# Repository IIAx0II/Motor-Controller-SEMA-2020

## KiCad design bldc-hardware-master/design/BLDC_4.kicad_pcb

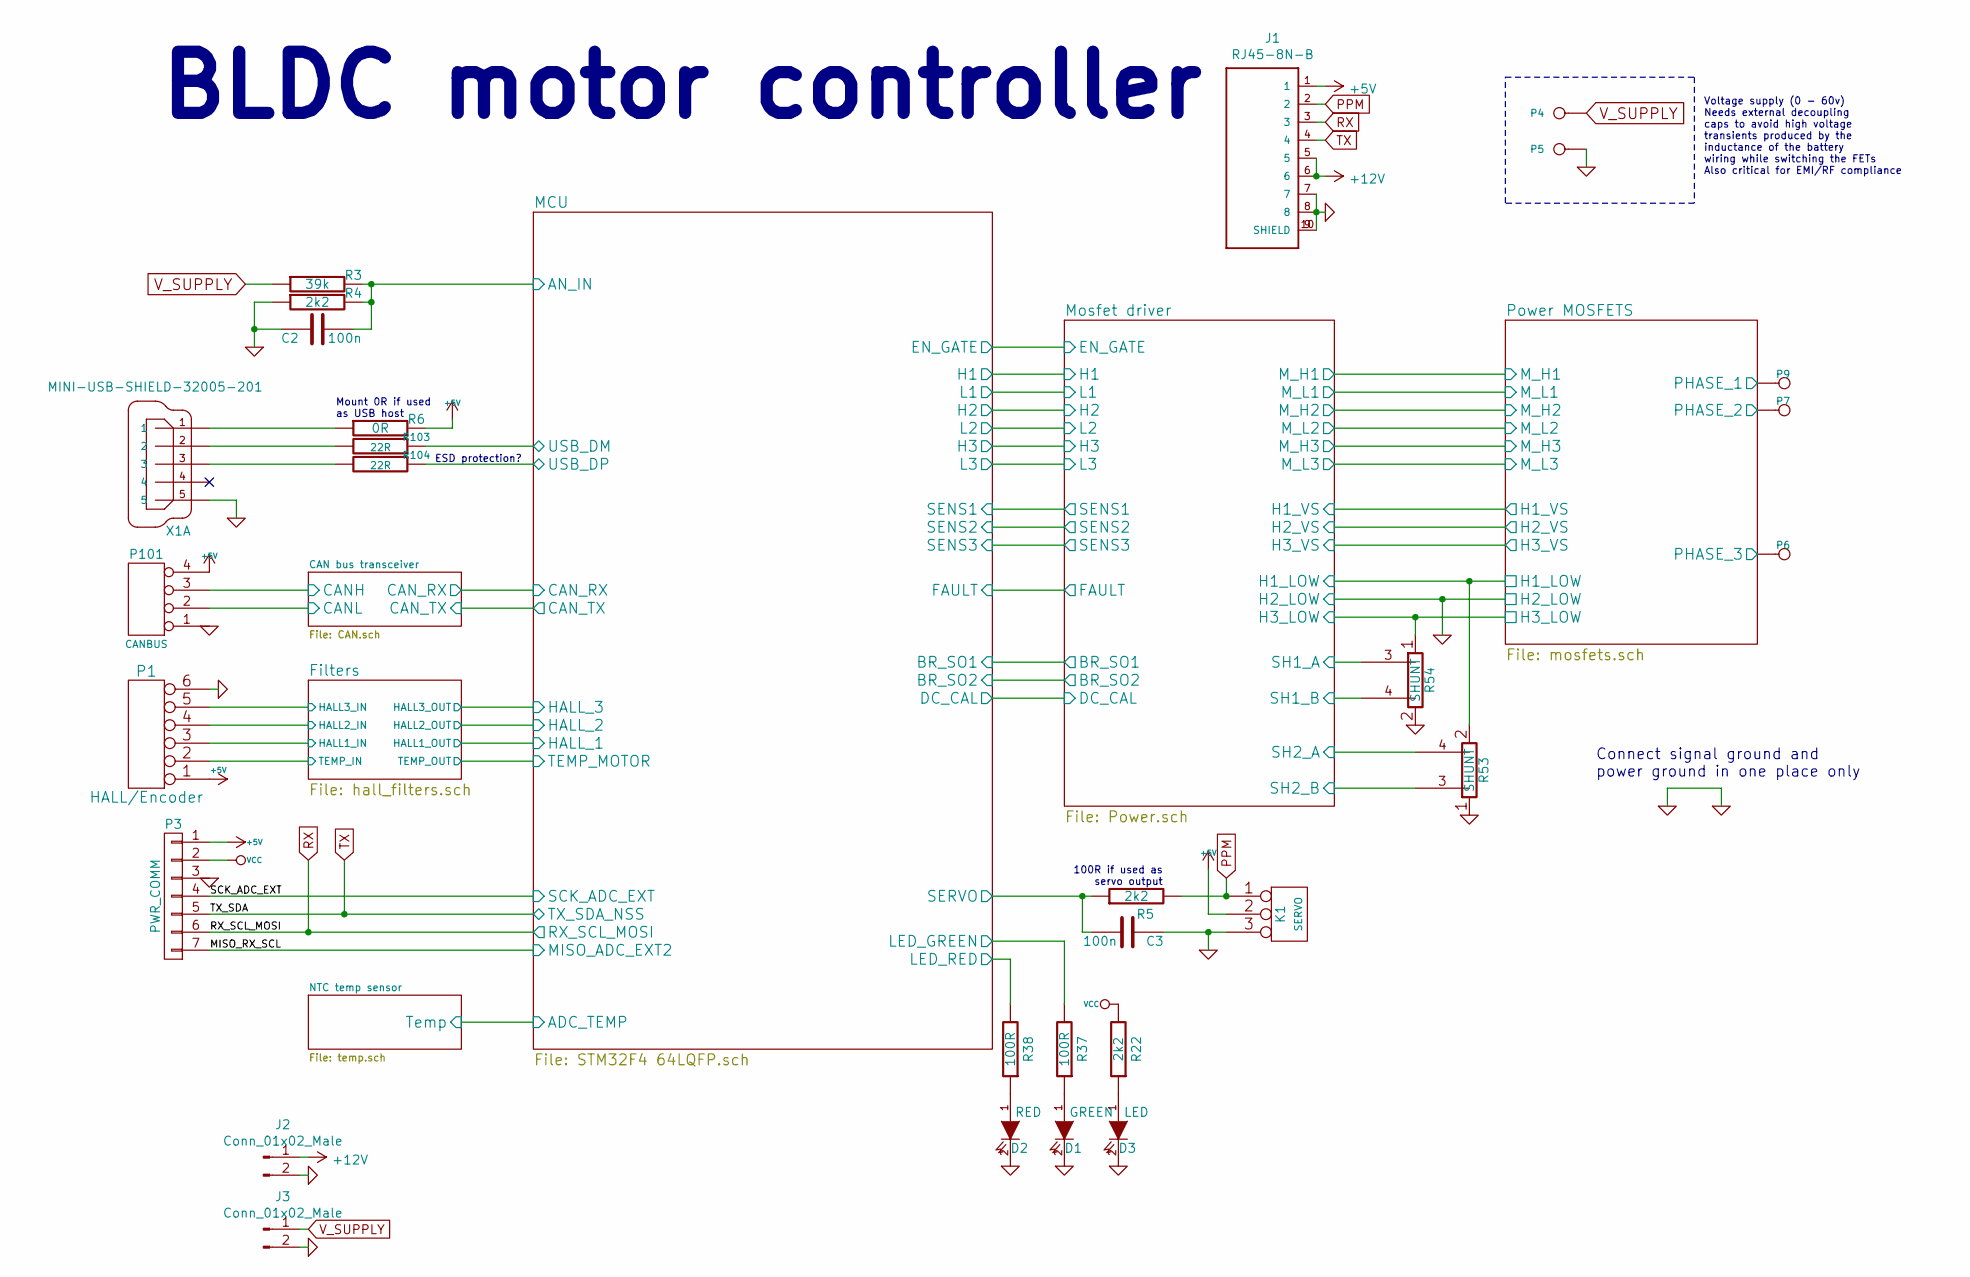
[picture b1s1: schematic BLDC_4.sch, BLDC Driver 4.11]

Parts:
C2, C3: 100n; SMD-0603_c
D1: GREEN; LED-0603
D2: RED; LED-0603
D3: LED; LED-0603
J1: RJ45-8N-B; TE_RJ45-8N-B
J2, J3: Conn_01x02_Male; Molex_Mini-Fit_Jr_5566-02A2_2x01_P4.20mm_Vertical
K1: SERVO; pinhead-1X03
P1: HALL/Encoder; MICRO_JST_6
P3: PWR_COMM; b7b-ph-kl
P4: IN+; 1PAD_4x5mm
P5: IN-; 1PAD_4x5mm
P6: MOTOR1; 1PAD_4x5mm
P7: MOTOR2; 1PAD_4x5mm
P9: MOTOR3; 1PAD_4x5mm
P101: CANBUS; b4b-ph-kl
R3: 39k; SMD-0603_r
R4, R5, R22: 2k2; SMD-0603_r
R6: 0R; SMD-0603_r
R37, R38: 100R; SMD-0603_r
R53, R54: SHUNT; WSLP2726
R103, R104: 22R; SMD-0603_r
X1: MINI-USB-SHIELD-32005-201; USB-UX60R-MB-5ST

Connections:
+5V: J1.1, K1.2 (PM), P1.1, P3.1, P101.4, R6.2; also elsewhere on the board
+12V: J1.5, J1.6, J2.1
/CAN bus transceiver/CANH: P101.3; also elsewhere on the board
/CAN bus transceiver/CANL: P101.2; also elsewhere on the board
/Filters/HALL1_IN: P1.3; also elsewhere on the board
/Filters/HALL2_IN: P1.4; also elsewhere on the board
/Filters/HALL3_IN: P1.5; also elsewhere on the board
/Filters/TEMP_IN: P1.2; also elsewhere on the board
/MCU/AN_IN: C2.2, R3.2, R4.2; also elsewhere on the board
/MCU/LED_GREEN: R37.2; also elsewhere on the board
/MCU/LED_RED: R38.2; also elsewhere on the board
/MCU/SERVO: C3.2, R5.1; also elsewhere on the board
/MCU/USB_DM: R103.1; also elsewhere on the board
/MCU/USB_DP: R104.1; also elsewhere on the board
/MISO_RX_SCL: P3.7; also elsewhere on the board
/Mosfet driver/H1_LOW: R53.2; also elsewhere on the board
/Mosfet driver/H1_VS: P9.1; also elsewhere on the board
/Mosfet driver/H2_VS: P7.1; also elsewhere on the board
/Mosfet driver/H3_LOW: R54.1; also elsewhere on the board
/Mosfet driver/H3_VS: P6.1; also elsewhere on the board
/Mosfet driver/SH1_A: R54.3; also elsewhere on the board
/Mosfet driver/SH1_B: R54.4; also elsewhere on the board
/Mosfet driver/SH2_A: R53.4; also elsewhere on the board
/Mosfet driver/SH2_B: R53.3; also elsewhere on the board
/SCK_ADC_EXT: P3.4; also elsewhere on the board
unnamed: D1.1 (A), R37.1
unnamed: D2.1 (A), R38.1
unnamed: D3.1 (A), R22.1
unnamed: R6.1, X1.1
unnamed: R103.2, X1.2
unnamed: R104.2, X1.3
PPM: J1.2, K1.1, R5.2
RX: J1.3, P3.6; also elsewhere on the board
TX: J1.4, P3.5; also elsewhere on the board
VCC: P3.2, R22.2; also elsewhere on the board
V_SUPPLY: J3.1, P4.1, R3.1; also elsewhere on the board

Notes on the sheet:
100R if used as servo output
Mount 0R if used as USB host
ESD protection?
BLDC motor controller
Voltage supply (0 - 60v) Needs external decoupling caps to avoid high voltage transients produced by the inductance of the battery wiring while switching the FETs Also critical for EMI/RF compliance
Connect signal ground and power ground in one place only

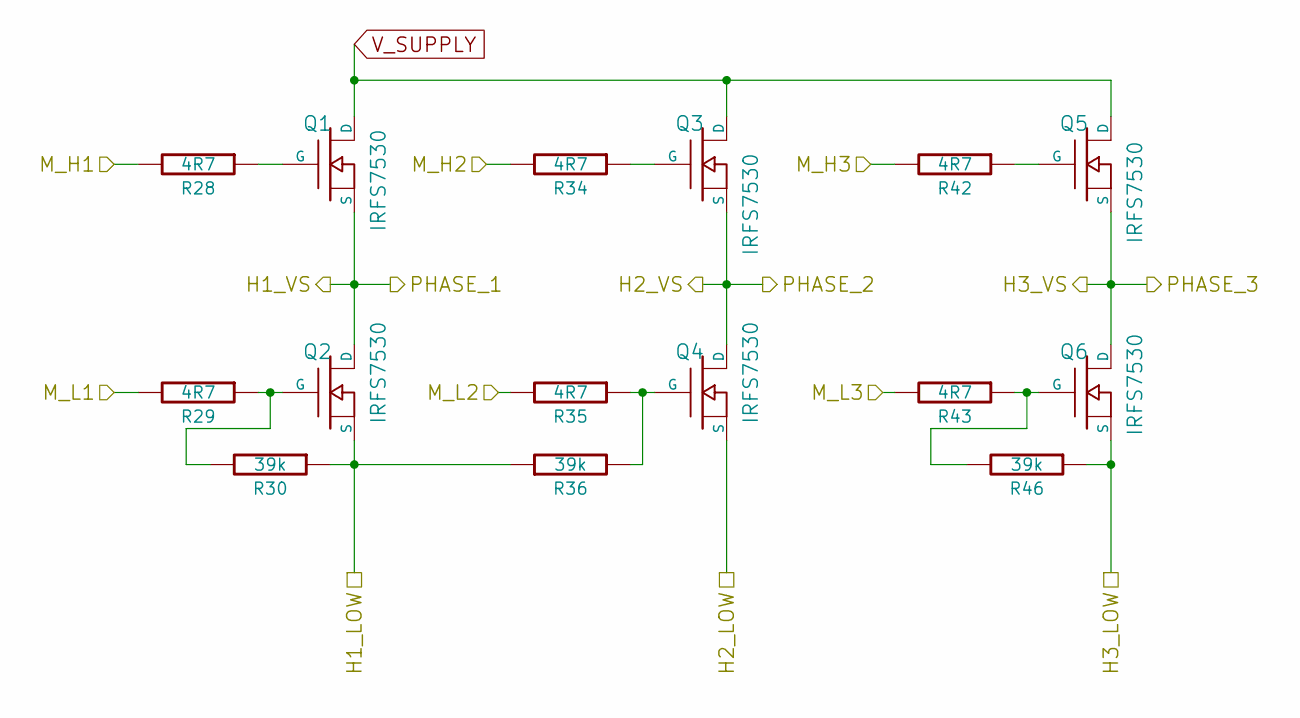
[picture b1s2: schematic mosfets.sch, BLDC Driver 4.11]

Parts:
Q1, Q2, Q3, Q4, Q5, Q6: IRFS7530; D2PAK-7-GDS
R28, R29, R34, R35, R42, R43: 4R7; SMD-0603_r
R30, R36, R46: 39k; SMD-0603_r

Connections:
/Mosfet driver/H1_LOW: Q2.S, R30.1, R36.1; also elsewhere on the board
/Mosfet driver/H1_VS: Q1.S, Q2.D; also elsewhere on the board
/Mosfet driver/H2_VS: Q3.S, Q4.D; also elsewhere on the board
/Mosfet driver/H3_LOW: Q6.S, R46.1; also elsewhere on the board
/Mosfet driver/H3_VS: Q5.S, Q6.D; also elsewhere on the board
/Mosfet driver/M_H1: R28.2; also elsewhere on the board
/Mosfet driver/M_H2: R34.2; also elsewhere on the board
/Mosfet driver/M_H3: R42.2; also elsewhere on the board
/Mosfet driver/M_L1: R29.2; also elsewhere on the board
/Mosfet driver/M_L2: R35.2; also elsewhere on the board
/Mosfet driver/M_L3: R43.2; also elsewhere on the board
unnamed: Q1.G, R28.1
unnamed: Q2.G, R29.1, R30.2
unnamed: Q3.G, R34.1
unnamed: Q4.G, R35.1, R36.2
unnamed: Q5.G, R42.1
unnamed: Q6.G, R43.1, R46.2
V_SUPPLY: Q1.D, Q3.D, Q5.D; also elsewhere on the board

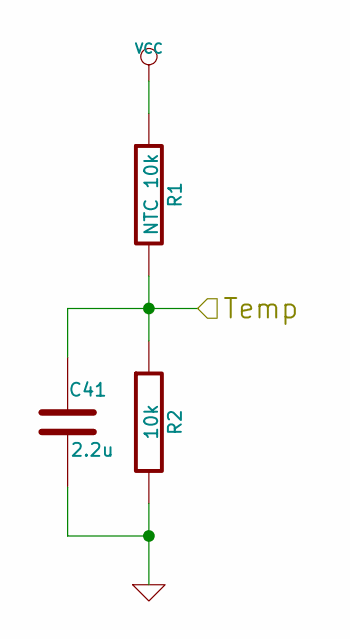
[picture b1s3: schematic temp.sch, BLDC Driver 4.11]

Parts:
C41: 2.2u; SMD-0603_c
R1: NTC 10k; SMD-0603_r
R2: 10k; SMD-0603_r

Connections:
/MCU/ADC_TEMP: C41.1, R1.2, R2.1; also elsewhere on the board
VCC: R1.1; also elsewhere on the board

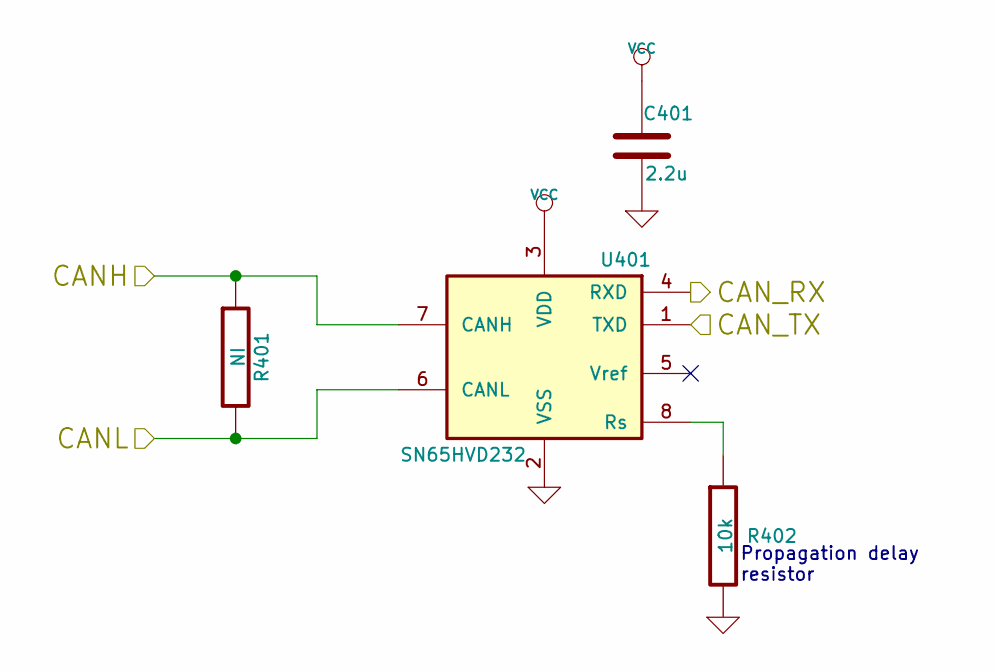
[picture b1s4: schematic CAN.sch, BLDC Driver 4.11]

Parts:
C401: 2.2u; SMD-0603_c
R401: NI; SMD-0603_r
R402: 10k; SMD-0603_r
U401: SN65HVD232; SOIC-8-W

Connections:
/CAN bus transceiver/CANH: R401.1, U401.7 (CANH); also elsewhere on the board
/CAN bus transceiver/CANL: R401.2, U401.6 (CANL); also elsewhere on the board
/CAN bus transceiver/CAN_RX: U401.4 (RXD); also elsewhere on the board
/CAN bus transceiver/CAN_TX: U401.1 (TXD); also elsewhere on the board
unnamed: R402.1, U401.8 (Rs)
VCC: C401.1, U401.3 (VDD); also elsewhere on the board

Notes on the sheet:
Propagation delay resistor

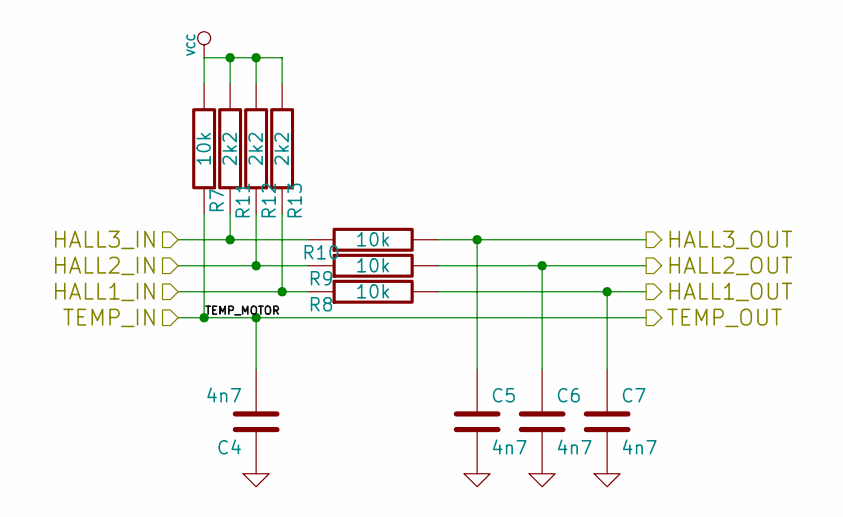
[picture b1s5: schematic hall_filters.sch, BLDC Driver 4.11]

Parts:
C4, C5, C6, C7: 4n7; SMD-0603_c
R7, R8, R9, R10: 10k; SMD-0603_r
R11, R12, R13: 2k2; SMD-0603_r

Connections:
/Filters/HALL1_IN: R8.1, R13.1; also elsewhere on the board
/Filters/HALL1_OUT: C7.1, R8.2; also elsewhere on the board
/Filters/HALL2_IN: R9.1, R12.1; also elsewhere on the board
/Filters/HALL2_OUT: C6.1, R9.2; also elsewhere on the board
/Filters/HALL3_IN: R10.1, R11.1; also elsewhere on the board
/Filters/HALL3_OUT: C5.1, R10.2; also elsewhere on the board
/Filters/TEMP_IN: C4.2, R7.1; also elsewhere on the board
VCC: R7.2, R11.2, R12.2, R13.2; also elsewhere on the board

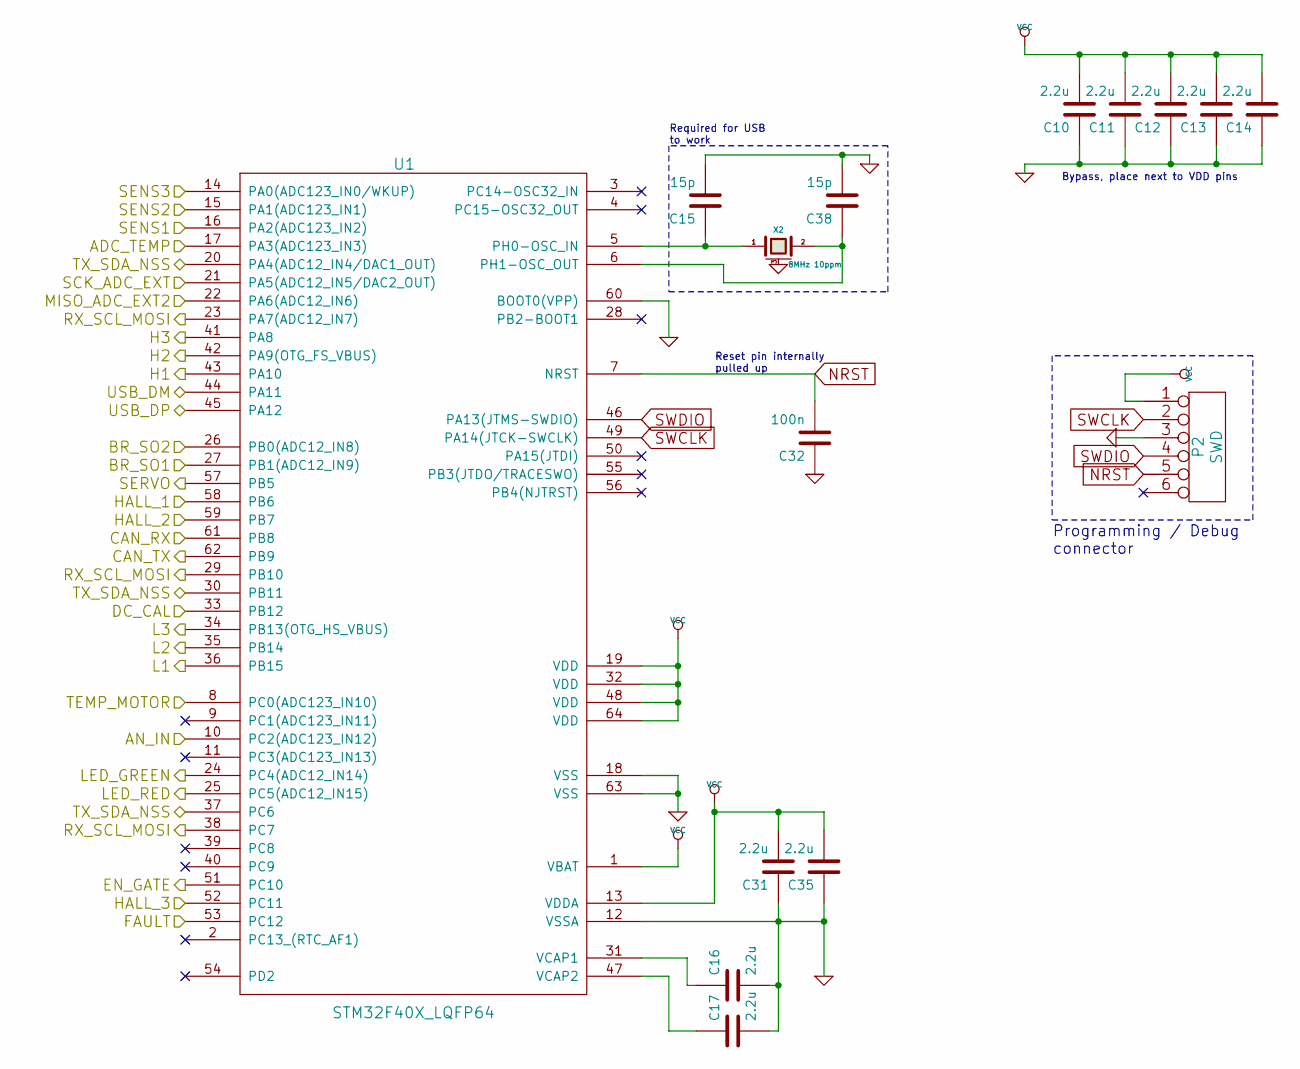
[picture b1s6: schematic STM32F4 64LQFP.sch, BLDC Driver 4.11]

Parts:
C10, C11, C12, C13, C14, C16, C17, C31, C35: 2.2u; SMD-0603_c
C15, C38: 15p; SMD-0603_c
C32: 100n; SMD-0603_c
P2: SWD; MICRO_JST_6
U1: STM32F40X_LQFP64; lqfp64_pad_mod
X2: 8MHz 10ppm; Crystal_5x3mm; mfg# ABM3B-8.0-10-1UT

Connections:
/CAN bus transceiver/CAN_RX: U1.61 (PB8); also elsewhere on the board
/CAN bus transceiver/CAN_TX: U1.62 (PB9); also elsewhere on the board
/Filters/HALL1_OUT: U1.58 (PB6); also elsewhere on the board
/Filters/HALL2_OUT: U1.59 (PB7); also elsewhere on the board
/Filters/HALL3_OUT: U1.52 (PC11); also elsewhere on the board
/Filters/TEMP_IN: U1.8 (PC0(ADC123_IN10)); also elsewhere on the board
/MCU/ADC_TEMP: U1.17 (PA3(ADC123_IN3)); also elsewhere on the board
/MCU/AN_IN: U1.10 (PC2(ADC123_IN12)); also elsewhere on the board
/MCU/BR_SO1: U1.27 (PB1(ADC12_IN9)); also elsewhere on the board
/MCU/BR_SO2: U1.26 (PB0(ADC12_IN8)); also elsewhere on the board
/MCU/DC_CAL: U1.33 (PB12); also elsewhere on the board
/MCU/EN_GATE: U1.51 (PC10); also elsewhere on the board
/MCU/FAULT: U1.53 (PC12); also elsewhere on the board
/MCU/H1: U1.43 (PA10); also elsewhere on the board
/MCU/H2: U1.42 (PA9(OTG_FS_VBUS)); also elsewhere on the board
/MCU/H3: U1.41 (PA8); also elsewhere on the board
/MCU/L1: U1.36 (PB15); also elsewhere on the board
/MCU/L2: U1.35 (PB14); also elsewhere on the board
/MCU/L3: U1.34 (PB13(OTG_HS_VBUS)); also elsewhere on the board
/MCU/LED_GREEN: U1.24 (PC4(ADC12_IN14)); also elsewhere on the board
/MCU/LED_RED: U1.25 (PC5(ADC12_IN15)); also elsewhere on the board
/MCU/SENS1: U1.16 (PA2(ADC123_IN2)); also elsewhere on the board
/MCU/SENS2: U1.15 (PA1(ADC123_IN1)); also elsewhere on the board
/MCU/SENS3: U1.14 (PA0(ADC123_IN0/WKUP)); also elsewhere on the board
/MCU/SERVO: U1.57 (PB5); also elsewhere on the board
/MCU/USB_DM: U1.44 (PA11); also elsewhere on the board
/MCU/USB_DP: U1.45 (PA12); also elsewhere on the board
/MISO_RX_SCL: U1.22 (PA6(ADC12_IN6)); also elsewhere on the board
/SCK_ADC_EXT: U1.21 (PA5(ADC12_IN5/DAC2_OUT)); also elsewhere on the board
NRST: C32.2, P2.5, U1.7 (NRST)
unnamed: C15.1, U1.5 (PH0-OSC_IN), X2.1
unnamed: C16.1, U1.31 (VCAP1)
unnamed: C17.1, U1.47 (VCAP2)
unnamed: C38.1, U1.6 (PH1-OSC_OUT), X2.2
RX: U1.23 (PA7(ADC12_IN7)), U1.29 (PB10), U1.38 (PC7); also elsewhere on the board
SWCLK: P2.2, U1.49 (PA14(JTCK-SWCLK))
SWDIO: P2.4, U1.46 (PA13(JTMS-SWDIO))
TX: U1.20 (PA4(ADC12_IN4/DAC1_OUT)), U1.30 (PB11), U1.37 (PC6); also elsewhere on the board
VCC: C10.2, C11.2, C12.2, C13.2, C14.2, C31.2, C35.2, P2.1, U1.1 (VBAT), U1.13 (VDDA), U1.19 (VDD), U1.32 (VDD), U1.48 (VDD), U1.64 (VDD); also elsewhere on the board

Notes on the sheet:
Programming / Debug connector
Reset pin internally pulled up
Required for USB to work
Bypass, place next to VDD pins

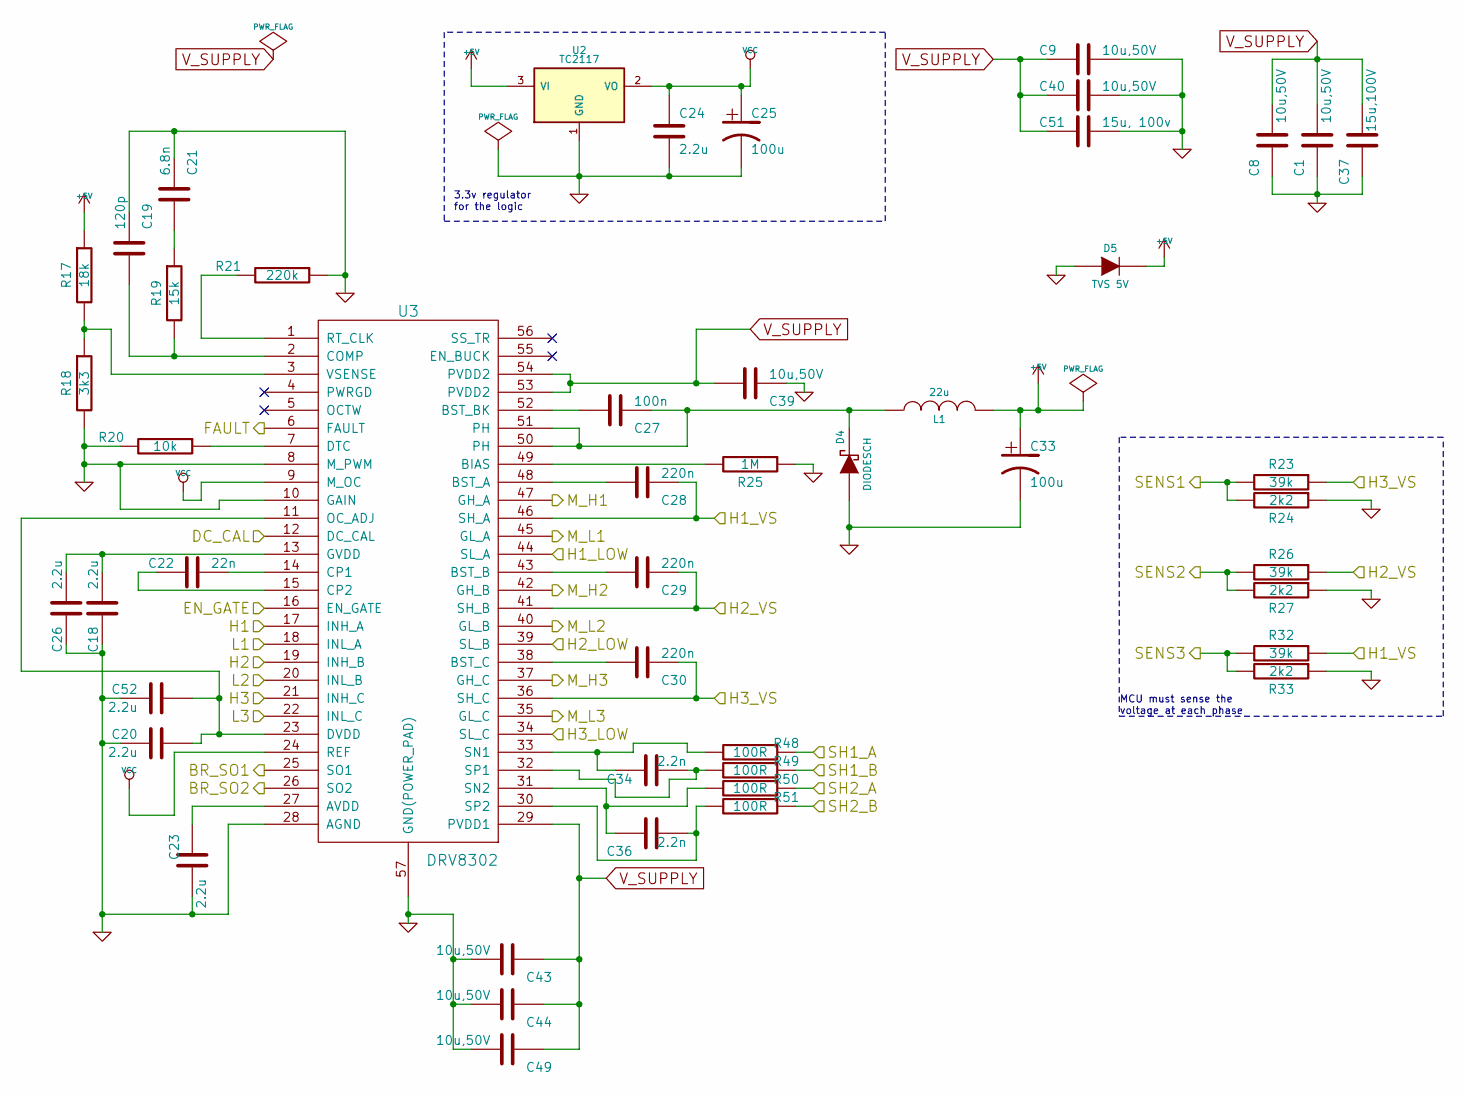
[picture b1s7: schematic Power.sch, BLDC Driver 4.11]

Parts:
C1, C8, C9, C39, C40, C43, C44, C49: 10u,50V; SMD-1206
C18, C20, C23, C24, C26, C52: 2.2u; SMD-0603_c
C19: 120p; SMD-0603_c
C21: 6.8n; SMD-0603_c
C22: 22n; SMD-0603_c
C25, C33: 100u; c_tant_B
C27: 100n; SMD-0603_c
C28, C29, C30: 220n; SMD-0603_c
C34, C36: 2.2n; SMD-0603_c
C37: 15u,100V; c_2220
C51: 15u, 100v; c_2220
D4: DIODESCH; SMA_Handsoldering
D5: TVS 5V; do214ac
L1: 22u; inductor_smd_8x5mm
R17: 18k; SMD-0603_r
R18: 3k3; SMD-0603_r
R19: 15k; SMD-0603_r
R20: 10k; SMD-0603_r
R21: 220k; SMD-0603_r
R23, R26, R32: 39k; SMD-0603_r
R24, R27, R33: 2k2; SMD-0603_r
R25: 1M; SMD-0603_r
R48, R49, R50, R51: 100R; SMD-0603_r
U2: TC2117; SOT-223
U3: DRV8302; TSSOP-56-PP

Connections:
+5V: C33.1, D5.2 (K), L1.2, R17.1, U2.3 (VI); also elsewhere on the board
/MCU/BR_SO1: U3.25 (SO1); also elsewhere on the board
/MCU/BR_SO2: U3.26 (SO2); also elsewhere on the board
/MCU/DC_CAL: U3.12 (DC_CAL); also elsewhere on the board
/MCU/EN_GATE: U3.16 (EN_GATE); also elsewhere on the board
/MCU/FAULT: U3.6 (FAULT); also elsewhere on the board
/MCU/H1: U3.17 (INH_A); also elsewhere on the board
/MCU/H2: U3.19 (INH_B); also elsewhere on the board
/MCU/H3: U3.21 (INH_C); also elsewhere on the board
/MCU/L1: U3.18 (INL_A); also elsewhere on the board
/MCU/L2: U3.20 (INL_B); also elsewhere on the board
/MCU/L3: U3.22 (INL_C); also elsewhere on the board
/MCU/SENS1: R23.2, R24.2; also elsewhere on the board
/MCU/SENS2: R26.2, R27.2; also elsewhere on the board
/MCU/SENS3: R32.2, R33.2; also elsewhere on the board
/Mosfet driver/H1_LOW: U3.44 (SL_A); also elsewhere on the board
/Mosfet driver/H1_VS: C28.1, R32.1, U3.46 (SH_A); also elsewhere on the board
/Mosfet driver/H2_VS: C29.1, R26.1, U3.41 (SH_B); also elsewhere on the board
/Mosfet driver/H3_LOW: U3.34 (SL_C); also elsewhere on the board
/Mosfet driver/H3_VS: C30.1, R23.1, U3.36 (SH_C); also elsewhere on the board
/Mosfet driver/M_H1: U3.47 (GH_A); also elsewhere on the board
/Mosfet driver/M_H2: U3.42 (GH_B); also elsewhere on the board
/Mosfet driver/M_H3: U3.37 (GH_C); also elsewhere on the board
/Mosfet driver/M_L1: U3.45 (GL_A); also elsewhere on the board
/Mosfet driver/M_L2: U3.40 (GL_B); also elsewhere on the board
/Mosfet driver/M_L3: U3.35 (GL_C); also elsewhere on the board
/Mosfet driver/SH1_A: R48.1; also elsewhere on the board
/Mosfet driver/SH1_B: R49.1; also elsewhere on the board
/Mosfet driver/SH2_A: R50.1; also elsewhere on the board
/Mosfet driver/SH2_B: R51.1; also elsewhere on the board
unnamed: C18.1, C26.1, U3.13 (GVDD)
unnamed: C19.2, R19.2, U3.2 (COMP)
unnamed: C20.2, C52.2, U3.11 (OC_ADJ), U3.23 (DVDD)
unnamed: C21.2, R19.1
unnamed: C22.1, U3.14 (CP1)
unnamed: C22.2, U3.15 (CP2)
unnamed: C23.2, U3.27 (AVDD)
unnamed: C27.1, D4.2 (K), L1.1, U3.50 (PH), U3.51 (PH)
unnamed: C27.2, U3.52 (BST_BK)
unnamed: C28.2, U3.48 (BST_A)
unnamed: C29.2, U3.43 (BST_B)
unnamed: C30.2, U3.38 (BST_C)
unnamed: C34.1, R48.2, U3.33 (SN1)
unnamed: C34.2, R49.2, U3.32 (SP1)
unnamed: C36.1, R50.2, U3.31 (SN2)
unnamed: C36.2, R51.2, U3.30 (SP2)
unnamed: R17.2, R18.1, U3.3 (VSENSE)
unnamed: R20.1, U3.7 (DTC)
unnamed: R21.2, U3.1 (RT_CLK)
unnamed: R25.2, U3.49 (BIAS)
VCC: C24.1, C25.1, U2.2 (VO), U3.9 (M_OC), U3.24 (REF); also elsewhere on the board
V_SUPPLY: C1.2, C8.2, C9.2, C37.2, C39.2, C40.2, C43.1, C44.1, C49.1, C51.2, U3.29 (PVDD1), U3.53 (PVDD2), U3.54 (PVDD2); also elsewhere on the board

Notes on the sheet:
MCU must sense the voltage at each phase
3.3v regulator for the logic

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
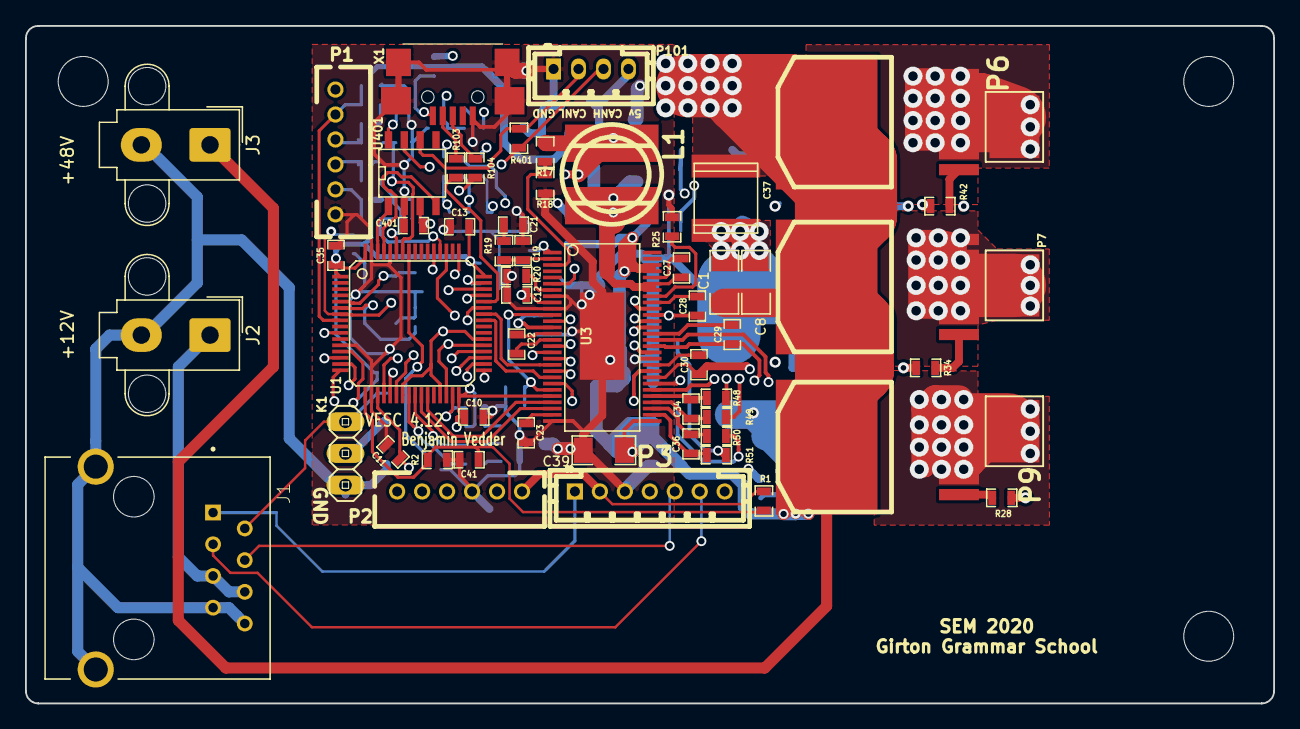
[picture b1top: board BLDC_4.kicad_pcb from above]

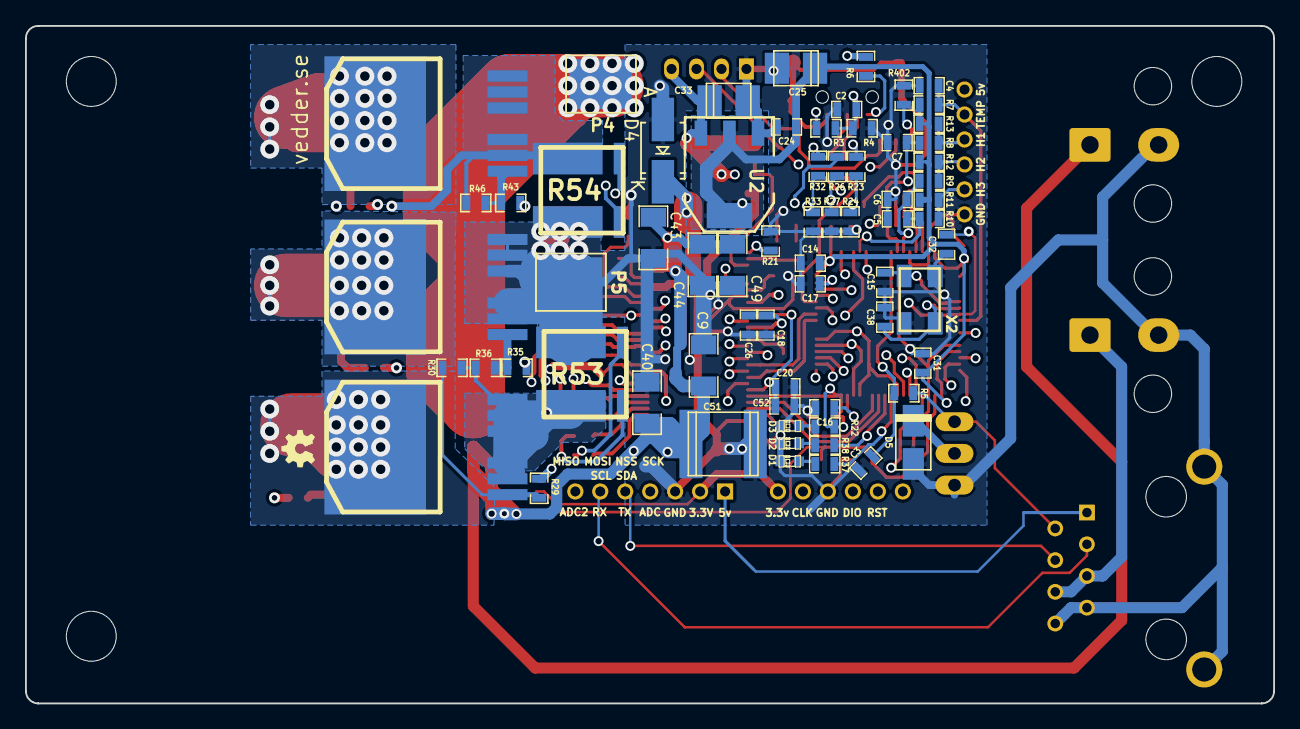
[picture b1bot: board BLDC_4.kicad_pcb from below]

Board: 4 copper layers, 100.0 x 54.3 mm, 128 parts (68 on the bottom side), 97 nets.

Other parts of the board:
 : MountingHole_4mm
 #2,  #3: MountingHole_4mm

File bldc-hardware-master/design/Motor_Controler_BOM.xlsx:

Part | Value | Package | Description | Qty | Place (YES/NO) | Distributor | Order Number | Comment
U1 |  | LQFP-64 | STM32F4 MCU | 1 | YES | MOUSER | 511-STM32F405RGT6
U2 |  | SOT-223-3 | VREG | 1 | YES | MOUSER | 579-TC2117-3.3VDBTR
U3 |  | HTSSOP-56-PP | MOSFET Driver | 1 | YES | MOUSER | 595-DRV8302DCA
U401 |  | SOIC-8 | CAN Transceiver | 1 | YES | MOUSER | 595-SN65HVD232DR
R1 |  | SM0603 | NTC resistor (temp sensor) | 1 | YES | MOUSER | 81-NCP18XH103F03RB
L1 |  | inductor_smd_8x5mm | Power Inductor | 1 | YES | MOUSER | 652-SDR0805-220ML
X1 |  | USB-UX60R-MB-5ST | Mini-USB | 1 | YES | MOUSER | 798-UX60R-MB-5ST
X2 | 8MHz | Crystal_5x3mm | Crystal 8MHz, 10PPM | 1 | YES | MOUSER | 815-ABM3B-8.0-10-1UT
Q1-Q6 | 60V 240A | D2PAK-7 | MOSFET 60V 240A | 6 | YES | MOUSER | 942-IRFS7530TRL7PP
R53,R54 | 1mOhm | WSLP2726 | Shunt 1mOhm | 2 | YES | MOUSER | 71-WSLP27261L000FEA
D5 | 5V | DO-214AC | TVS diode 5V | 1 | YES | MOUSER | 576-SMAJ5.0A
D4 | 60V 2A | DO-214AA(SMB) | Shottky 60V 2A | 1 | YES | MOUSER | 771-PMEG6020ER-115 | Voltage and current important
C25,C33 | 100uF, 6.3V | c_tant_B | CAP 100u, 6.3V | 2 | YES | MOUSER | 581-TPSB107K006R0400 | Voltage important
C1,C8,C9,C39,C40,C43,C44,C49 | 10uF 50V | SMD1206 | CAP 10u, 50V, 1206 | 8 | YES | MOUSER | 963-UMK316BBJ106ML-T | Voltage important
C37,C51 | 15uF, 100V | SMD-2220 | CAP 15u, 100V, 2220 | 2 | YES | MOUSER | 810-CGA9P3X7S2A156M | Voltage important
C2,C3,C27,C32 | 100nF, 50V | SMD-0603 | CAP 100n, 50V, 0603 | 4 | YES | MOUSER | 581-06035C104JAT2A | Voltage important
C28,C29,C30 | 220nF,25V | SMD-0603 | CAP 220n, 25V, 0603 | 3 | YES | MOUSER | 963-TMK107B7224KA-T | Voltage important
C24,C10,C11,C12,C13,C14,C16,C17,C18,C20,C23,C26,C31,C35,C41,C52,C401 | 2.2uF, 16V | SMD-0603 | CAP 2.2u, 16V, 0603 | 17 | YES | MOUSER | 810-C1608X5R1C225M | Voltage important
P3 |  | MICRO_JST_7 | Micro-JST 7PIN 2mm | 1 | YES | FARNELL | 9491864 | Can be found on ebay
P1,P2 |  | MICRO_JST_6 | Micro-JST 6PIN 2mm | 2 | YES | FARNELL | 9492453 | Can be found on ebay
P101 |  | MICRO_JST_4 | Micro-JST 4PIN 2mm | 1 | YES | FARNELL | 9492437 | Can be found on ebay
C4-C7 | 4.7nF, 50V | SMD-0603 | CAP 4.7n, 50V, 0603 | 4 | YES | MOUSER | 81-GRM39X472J50D
C34, C36 | 2.2nF, 50V | SMD-0603 | CAP 2.2n, 50V, 0603 | 2 | YES | MOUSER | 81-GRM39X222J50D
C15,C38 | 15pF, 100V | SMD-0603 | CAP 15p, 100V, 0603 | 2 | YES | MOUSER | 81-GRM1885C2A150JA01
C19 | 120pF, 50V | SMD-0603 | CAP 120p, 50V, 0603 | 1 | YES | MOUSER | 81-GRM39C121J50
C21 | 6.8nF, 50V | SMD-0603 | CAP 6.8n, 50V, 0603 | 1 | YES | MOUSER | 81-GRM18R71H682KA01J
C22 | 22nF, 50V | SMD-0603 | CAP 22n, 50V, 0603 | 1 | YES | MOUSER | 81-GRM18F51H223ZA01D
D1 |  | SMD-0603 | LED Green, 0603 | 1 | YES | MOUSER | 859-LTST-C191KGKT
D2 |  | SMD-0603 | LED Red, 0603 | 1 | YES | MOUSER | 859-LTST-C191KRKT
D3 |  | SMD-0603 | LED Blue, 0603 | 1 | YES | MOUSER | 720-LBQ39GN1P1351
R28,R29,R34,R35,R42,R43 | 4.7ohm | SMD-0603 | R 4.7ohm, 0603 | 6 | YES | MOUSER | 660-RK73H1JTTD4R70F
R37,R38,R48-R51,R401 | 100ohm | SMD-0603 | R 100ohm, 0603 | 7 | YES | MOUSER | 660-RK73H1JTTD1000F
R4,R5,R11,R12,R13,R22,R24,R27,R33 | 2.2kOhm | SMD-0603 | R 2.2k, 0603 | 9 | YES | MOUSER | 660-RK73H1JTTD2201F
R18 | 3.3kOhm | SMD-0603 | R 3.3k, 0603 | 1 | YES | MOUSER | 660-RK73H1JTTD3301F
R2,R7,R8,R9,R10,R20,R402 | 10kOhm | SMD-0603 | R 10k, 0603 | 7 | YES | MOUSER | 660-RK73H1JTTD1002F
R19 | 15kOhm | SMD-0603 | R 15k, 0603 | 1 | YES | MOUSER | 660-RK73H1JTTD1502F
R17 | 18kOhm | SMD-0603 | R 18k, 0603 | 1 | YES | MOUSER | 660-RK73H1JTTD1802F
R3,R23,R26,R30,R32,R36,R46 | 39kOhm | SMD-0603 | R 39k, 0603 | 7 | YES | MOUSER | 667-ERJ-3EKF3902V
R21 | 220kOhm | SMD-0603 | R 220k, 0603 | 1 | YES | MOUSER | 660-RK73H1JTTD2203F
R25 | 1MOhm | SMD-0603 | R 1M, 0603 | 1 | YES | MOUSER | 660-RK73H1JTTD1004F
R103, R104 | 22ohm | SMD-0603 | R 22R, 0603 | 2 | YES | MOUSER | 660-RK73H1JTTD22R0F
J2,J3 |  | MINI_FIT_JR_2_S | Mini-fit-jr 2pin socket | 2 | YES | MOUSER | 538-39-30-6025
J1 |  | RJ45 |  | 1
Extra |  | MINI_FIT_JR_2_P | Mini-fit-jr 2pin plug | 2 |  | MOUSER | 538-39-01-2020
Driver Controler
Part | Qty | Link
Arduino Nano | 1 | https://www.banggood.com/ATmega328P-Nano-V3-Module-Improved-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
doit esp32 devkit v1 | 1 | https://www.banggood.com/ESP32-Development-Board-WiFibluetoo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
Micro SD card reader/writer | 1 | https://www.banggood.com/Micro-TF-Card-Memory-Shield-Module-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
LCD 20x4 | 1 | https://www.banggood.com/IIC-I2C-2004-204-20-x-4-Character-L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
RJ45 | 1

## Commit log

2019-10-21 Copy from local file
2020-02-16 Commit #1
2020-02-16 generated cam files
